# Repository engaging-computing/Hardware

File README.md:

Hardware
========

Hardware projects relating to isenseproject.org

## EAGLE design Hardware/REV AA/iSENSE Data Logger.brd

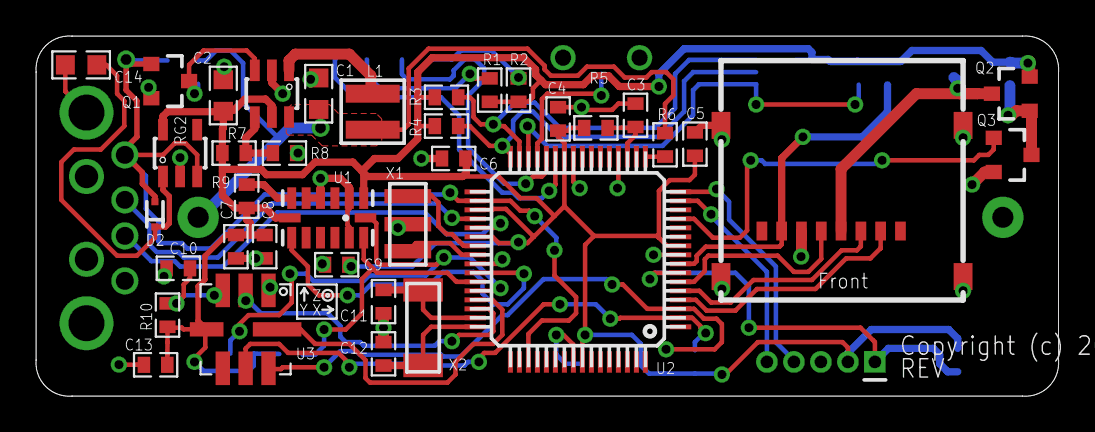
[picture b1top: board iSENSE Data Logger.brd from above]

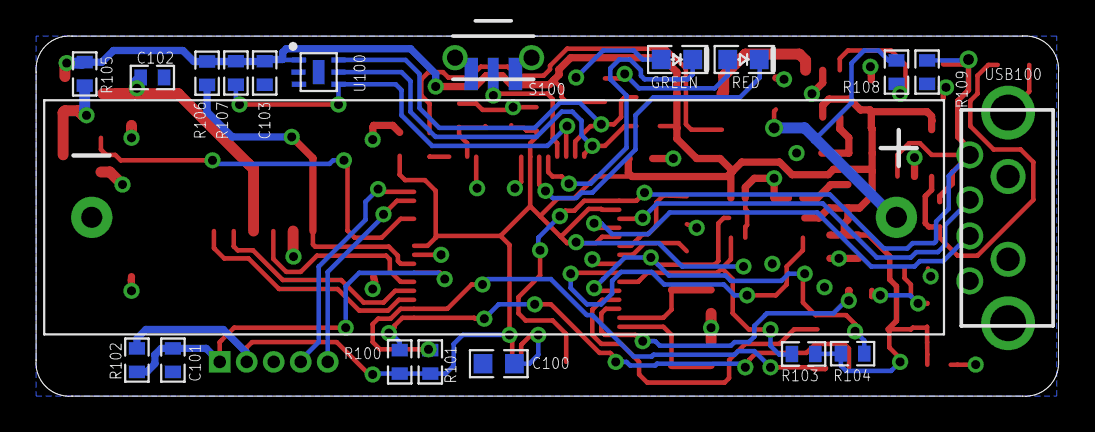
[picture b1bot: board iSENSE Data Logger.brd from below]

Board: 2 copper layers, 56.8 x 20.0 mm, 59 parts (20 on the bottom side), 44 nets.

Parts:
BAT: BATTERY_HOLDER_AAA_KEYSTONE_2466_NO_HOLES
C1, C100: 10u; RCL_0603
C2: 47u; RCL_0603
C3, C4, C5, C6, C8, C9, C10, C13, C101: 0.1u; RCL_0402
C7, C103: 1.0u; RCL_0402
C11, C12: 20pF; RCL_0402
C14: 1.0u; RCL_0603
C102: 10u; RCL_0402
CON1: SOCKET_SD_CARD_MICRO-AMP-101-00303-68; SOCKET_SD_CARD_MICRO
D2: SOD523
GREEN: GREEN; LED_0603
ICSP1: PIC-ICSP-MINI
L1: 4.7u; INDUCTOR_3MM_X_3MM
Q1, Q3: FDV305N; SOT23-3
Q2: FDV304P; SOT23-3
R1, R2, R6: 1k; RCL_0402
R3, R4, R100, R101, R103, R104: 2.2k; RCL_0402
R5: 10; RCL_0402
R7: 536k; RCL_0402
R8: 309k; RCL_0402
R9: 22; RCL_0402
R10: 50; RCL_0402
R102, R106, R107: 10k; RCL_0402
R105: 330k; RCL_0402
R108, R109: 100k; RCL_0402
RED: RED; LED_0603
RG1: MCP1640-SOT23-6; SOT23-6
RG2: 3.3V; SOT23-5
S100: SWITCH_MOMENTARY-SMD-RA; SWITCH_TACTILE_SMD_RA
U1: ADXL345; LGA14
U2: PIC24FJ128GB106-TQFP64; TQFP64-10X10
U3: BMP085
U100: MAX44007; UTDFN-OPTO
U$100: INFO_BOARD1
USB100: CON_USB_4_PIN-A_MALE; CON_USB_A_MALE_CNC_TECH_1001-010-01001
X1: CERAMIC_RESONATOR_MURATA_2X4.5
X2: CRYSTAL_ABRACON_ABS10

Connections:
+3V3: C2.1, C4.2, C5.1, C6.2, C7.2, C8.2, C9.1, C13.2, C103.1, ICSP1.2, Q2.2, R1.1, R2.1, R3.2, R4.2, R5.2, R7.1, R9.1, R10.2, R100.2, R101.2, R102.2, R103.2, R104.2, R105.2, R106.1, R107.2, RG1.5, RG2.5, U1.1, U1.7, U2.10, U2.26, U2.35, U2.38, U2.57, U3.4, U100.1
ADXL_INT1: U1.8, U2.42
BAT_MON: R6.2, U2.17
BMP085_EOC: U2.46, U3.2
BMP085_XCLR: U2.45, U3.8
GND: BAT.-, C1.2, C2.2, C3.1, C4.1, C5.2, C6.1, C7.1, C8.1, C9.2, C10.1, C11.2, C12.2, C13.1, C14.2, C100.2, C101.2, C102.1, C103.2, CON1.6, CON1.SHIELD1, CON1.SHIELD2, CON1.SHIELD3, CON1.SHIELD4, ICSP1.3, Q1.2, Q3.2, R8.2, R109.2, RG1.2, RG2.2, S100.1, U1.2, U1.4, U1.5, U1.12, U2.9, U2.20, U2.25, U2.41, U3.1, U100.2, U100.3, U100.EP, USB100.GND, USB100.MTN1, USB100.MTN2, USB100.MTN3, USB100.MTN4, X1.2
LIGHT_INT: R107.1, U2.30, U100.4
unnamed: Q1.3, R108.2, RG1.3
unnamed: R9.2, U1.6
unnamed: C10.2, R10.1, U3.3
unnamed: GREEN.A, R2.2
unnamed: U2.39, X1.1
unnamed: R1.2, RED.A
unnamed: C14.1, D2.C, RG2.1
unnamed: BAT.+, C1.1, L1.1, R6.1, R108.1, RG1.6
unnamed: L1.2, RG1.1
unnamed: R7.2, R8.1, RG1.4
unnamed: GREEN.C, U2.28
unnamed: RED.C, U2.27
unnamed: C11.1, U2.47, X2.1
unnamed: C12.1, U2.48, X2.2
unnamed: S100.2, U2.29
unnamed: C102.2, CON1.4, Q2.3
unnamed: Q2.1, Q3.3, R105.1
unnamed: U2.40, X1.3
unnamed: ICSP1.5, U2.15
unnamed: C100.1, U2.56
unnamed: C3.2, R5.1, U2.19
unnamed: C101.1, ICSP1.1, R102.1, U2.7
unnamed: ICSP1.4, U2.16
unnamed: U2.37, USB100.D+
unnamed: U2.36, USB100.D-
SCL1: R104.1, U1.14, U2.44
SCL2: R4.1, U2.32, U100.5
SCL3: R100.1, U2.2, U3.6
SDA1: R103.1, U1.13, U2.43
SDA2: R3.1, U2.31, U100.6
SDA3: R101.1, U2.3, U3.7
SD_CLK: CON1.5, U2.6
SD_CS: CON1.2, U2.4
SD_DI: CON1.3, U2.5
SD_DO: CON1.7, R106.2, U2.8
SD_PWR: Q3.1, U2.13
USB_ATTACH: D2.A, Q1.1, R109.1, RG2.3, U2.34, U2.51, USB100.VUSB

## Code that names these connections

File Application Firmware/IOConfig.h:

#ifndef __IOCONFIG_H__
#define __IOCONFIG_H__

    #define INPUT_PIN 1
    #define OUTPUT_PIN 0

    /** I/O pin definitions ********************************************/
    #define BUTTON_TRIS			TRISBbits.TRISB14
    #define LED_RED_TRIS		TRISBbits.TRISB12
    #define LED_GREEN_TRIS		TRISBbits.TRISB13
    #define BUTTON				PORTBbits.RB14
    #define LED_RED				PORTBbits.RB12
    #define LED_GREEN			PORTBbits.RB13

	#define SD_PWR_TRIS			TRISBbits.TRISB3
	#define SD_PWR				PORTBbits.RB3

	#define BMP085_EOC_TRIS		TRISDbits.TRISD0
	#define BMP085_XCLR_TRIS	TRISDbits.TRISD11
	#define BMP085_EOC			PORTDbits.RD0
	#define BMP085_XCLR			PORTDbits.RD11

	#define ADXL_INTR_TRIS		TRISDbits.TRISD8
	#define ADXL_INTR			PORTDbits.RD8

	#define LIGHT_INTR_TRIS		TRISBbits.TRISB15
	#define LIGHT_INTR			PORTBbits.RB15

    /*******************************************************************/
    /******** USB stack hardware selection options *********************/
    /*******************************************************************/
    //This section is the set of definitions required by the MCHPFSUSB
    //  framework.  These definitions tell the firmware what mode it is
    //  running in, and where it can find the results to some information
    //  that the stack needs.
    //These definitions are required by every application developed with
    //  this revision of the MCHPFSUSB framework.  Please review each
    //  option carefully and determine which options are desired/required
    //  for your application.

    //#define USE_SELF_POWER_SENSE_IO
    //#define tris_self_power     TRISAbits.TRISA2    // Input
    #define self_power          1

    #define USE_USB_BUS_SENSE_IO
    #define tris_usb_bus_sense  TRISDbits.TRISD3    // Input
    #define USB_BUS_SENSE       PORTDbits.RD3 

    //Uncomment this to make the output HEX of this project 
    //   to be able to be bootloaded using the HID bootloader
    #define PROGRAMMABLE_WITH_USB_HID_BOOTLOADER	

    //If the application is going to be used with the HID bootloader
    //  then this will provide a function for the application to 
    //  enter the bootloader from the application (optional)
    #if defined(PROGRAMMABLE_WITH_USB_HID_BOOTLOADER)
        #define EnterBootloader() __asm__("goto 0x400")
    #endif   

    /*******************************************************************/
    /******** MDD File System selection options ************************/
    /*******************************************************************/
    #define USE_SD_INTERFACE_WITH_SPI

    // SD Card connections
    #define SD_CS				PORTGbits.RG6
    #define SD_CS_TRIS			TRISGbits.TRISG6
    
    //#define SD_CD				PORTCbits.RC15
    //#define SD_CD_TRIS		TRISCbits.TRISC15
    #define SD_CD               0
   
    //#define SD_WE				PORTFbits.RF1
    //#define SD_WE_TRIS		TRISFbits.TRISF1
    #define SD_WE				0

    // Registers for the SPI module we are using
    #define SPICON1				SPI2CON1
    #define SPISTAT				SPI2STAT
    #define SPIBUF				SPI2BUF
    #define SPISTAT_RBF			SPI2STATbits.SPIRBF
    #define SPICON1bits			SPI2CON1bits
    #define SPISTATbits			SPI2STATbits
    #define SPIENABLE           SPISTATbits.SPIEN

    // Tristate pins for SCK/SDI/SDO lines
    #define SPICLOCK			TRISGbits.TRISG8
    #define SPIIN				TRISGbits.TRISG9
    #define SPIOUT			    TRISGbits.TRISG7

	// Clock frequency
    #define CLOCK_FREQ 32000000
//    #define CLOCK_FREQ 16000000
    #define GetSystemClock() CLOCK_FREQ
    #define GetInstructionClock() GetSystemClock()

    /** MDD File System error checking *********************************/
    // Will generate an error if the clock speed is too low to interface to the card
    #if (GetSystemClock() < 100000)
        #error Clock speed must exceed 100 kHz
    #endif 

#endif  // __IOCONFIG_H__

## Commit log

2012-12-27 Initial upload of all files.
2012-12-28 Added Host Software.
2013-01-09 Added Masters Thesis PDF
2013-01-24 modified eagle files, new cap value for C2, saved in version 6.3
2013-02-06 updated comments in code
2013-02-11 First commit: Mac host software
    currently, time and date are read off connected uPPT, and displayed in
    the UI
2013-02-11 Battery Voltage outputting to UI
    data incorrect for now
2013-02-13 temperature data now goes to UI
    Batt Voltage and Temperature are both incorrect data still
2013-02-15 Added code for set date/time
    not exactly working yet
2013-02-19 fixed date/time information before it's sent to the uPPT
    still doesn't seem to be pushing to the device correctly, but at least
    the data is correct first
2013-02-20 Correction
    setting date and time now seems to work
2013-02-20 Test LEDs button implemented and working
    involved creating a sendGenericCommand method, so subsequent
    single-byte commands to the PINPoint should work with no problems. Also
    commented lots of things
2013-02-20 Read Button diagnostic command works
    involved writing a function to allow text output to the results console
    in the diagnostics tab
2013-02-20 added console message when Test LED button is pressed
2013-02-20 added a script to get the hex file from the uppt, added the binaries from the uppt, updated gitignore to ignore object files
2013-02-20 added documentation files, such as data sheets and a picture of how to program the device
2013-02-21 moved binaries so the cleanup script wouldn't delete them
2013-02-21 deleting temp files
2013-02-21 forgot this file in the last commit
2013-02-22 fixed diagnostics console
    now has monospace font, is scrollable, and non-editable by the user
2013-02-22 Read Battery Voltage button now works
    note: adding cases to switch for these diagnostics messages has broken
    time/date, but they go back to normal if the cases are removed. It's
    under investigation
2013-02-25 Fixed lots of things
    Moved input report callback to main function rather than a separate
    class, fixed all date/time/battery voltage/temperature problems. Added
    Check RTCC button
2013-02-25 Added pressure to UI
    fixed Battery Voltage diagnostics button which was actually broken from
    previous commit
2013-02-25 added altitude to UI output
    altitude data seems incorrect, and looking into it more, pressure data
    seems that it may also be incorrect
2013-02-27 All values for READ_ALL are being pulled off pinpoint and piped to UI
    values for pressure onwards are currently incorrect
2013-02-27 Implemented buttons for scanning MAX, BMP, and ADXL sensors in diagnostics panel
2013-02-28 made a light flash
2013-03-01 Added function that disables/enables all buttons based on PPT connection status
2013-03-01 Fixed pressure!
    somehow
2013-03-01 broke pressure again
    but I think I'm doing things more correctly now
2013-03-04 Read System Info button implemented
    the data read in from this is also wrong……….
2013-03-04 Fixed all values reading in wrong from uPPT
    turns out I don't know how malloc works. everything implemented is now
    working as expected!
2013-03-06 Implemented Run Full Diagnostics button
2013-03-06 set up tab view to hold graphs
2013-03-14 Added message when running diagnostics
2013-03-14 Project now builds with CorePlot library
2013-03-18 Empty graphs now drawing in main tab
    need to modify properties, and add data, but so far so good
2013-03-18 Added basic theming and drop shadow to graph views
2013-03-20 Lots of graph formatting
    Light graph almost entirely formatted
2013-03-22 working on getting data into the graphs
    this is more complicated than I thought it would be
2013-03-25 Live data is plotting on the light graph!
    X-axis range doesn't yet update when the plot goes off the end
2013-03-25 Light Graph completely functional
    looks right, acts right
2013-03-25 Temperature graph up and running
    only 6 graphs left to implement
2013-03-27 All graphs on the main tab are working
    Just have to add accelerometer graphs now
2013-03-29 Hid diagnostics panel controls that don't have source code in the Windows app
    if I ever find out what to do with them they can be unhidden easily
2013-03-29 Acceleration graph done
    App is now feature-complete, ready for testing
2013-03-29 Added a legend to the acceleration plots
2013-03-29 added drop shadow to accel graph to match other graphs
2013-04-01 App doesn't crash when PINPoint is unplugged
    Instead it pauses collecting data and greys out the buttons
2013-04-01 Added coreplot to build, added icon to application, added builds folder
2013-04-03 Made uPINPoint app not resizable, because it breaks layout
2014-01-23 moved all hardware related folders to subfolder Hardware
2014-05-28 Fixed bugs in Android CRP
2014-07-11 Readded the hardware files as a single directory
2014-07-12 Preserving readme and .gitignore
2014-07-13 Cleaning up repo to prep for merge of uPINPoint repo
2014-07-13 Reorganized the uPINPoint repo in prep to merge into isenseDev/Hardware
2014-07-13 Reorganized the repo in prep to merge with isenseDev/uPINPoint-1.0
2014-07-13 moved .gitignore

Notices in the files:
Hardware/REV AA/iSENSE Data Logger.brd:
COPYRIGHT: Copyright (c) 2012
